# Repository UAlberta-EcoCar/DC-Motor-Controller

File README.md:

# DC-Motor-Controller
Our custom DC brushed motor controller

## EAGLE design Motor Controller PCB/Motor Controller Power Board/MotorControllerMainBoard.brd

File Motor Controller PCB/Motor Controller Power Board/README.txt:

If we deside to use an external mountable PCB for the voltage regulators,
it'll go here.

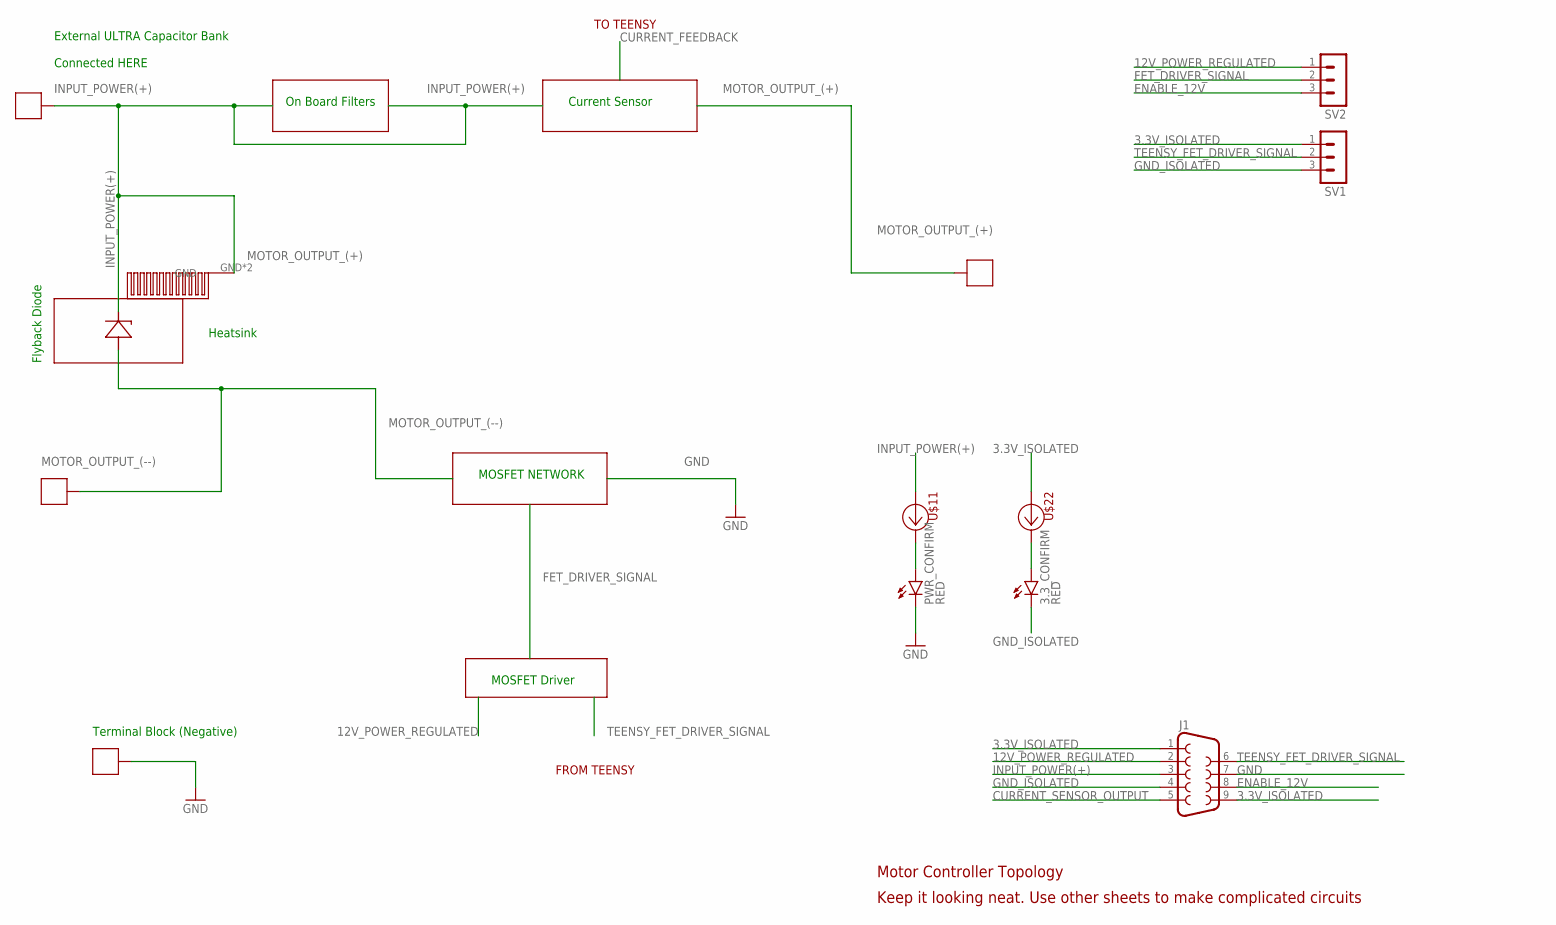
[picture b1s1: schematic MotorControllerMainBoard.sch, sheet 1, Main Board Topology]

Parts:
3.3_CONFIRM: RED; LED-1206
J1: DB9FEMALE; DB9
PWR_CONFIRM: RED; LED-1206
SV1, SV2: MA03-1
U$5: FLYBACK; TO
U$11, U$22: AL5809-20S1-7; SOD-123
U$12, U$14, U$15, U$16: 74650073R
U$23: DA-T263-101E

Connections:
3.3V_ISOLATED: J1.1, J1.9, SV1.1, U$22.A; also elsewhere on the board
12V_POWER_REGULATED: J1.2, SV2.1; also elsewhere on the board
CURRENT_SENSOR_OUTPUT: J1.5; also elsewhere on the board
ENABLE_12V: J1.8, SV2.3; also elsewhere on the board
FET_DRIVER_SIGNAL: SV2.2; also elsewhere on the board
GND: J1.7, PWR_CONFIRM.C, U$15.P$1, U$15.P$2, U$15.P$3, U$15.P$4; also elsewhere on the board
GND_ISOLATED: 3.3_CONFIRM.C, J1.4, SV1.3; also elsewhere on the board
INPUT_POWER(+): J1.3, U$5.CATHODE, U$11.A, U$14.P$1, U$14.P$2, U$14.P$3, U$14.P$4, U$23.GND, U$23.GND2\; also elsewhere on the board
MOTOR_OUTPUT_(+): U$16.P$1, U$16.P$2, U$16.P$3, U$16.P$4; also elsewhere on the board
MOTOR_OUTPUT_(--): U$5.ANODE, U$12.P$1, U$12.P$2, U$12.P$3, U$12.P$4; also elsewhere on the board
unnamed: 3.3_CONFIRM.A, U$22.C
unnamed: PWR_CONFIRM.A, U$11.C
TEENSY_FET_DRIVER_SIGNAL: J1.6, SV1.2; also elsewhere on the board

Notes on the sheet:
Current Sensor
On Board Filters
Flyback Diode
MOSFET NETWORK
MOSFET Driver
TO TEENSY
FROM TEENSY
External ULTRA Capacitor Bank Connected HERE
Motor Controller Topology
Keep it looking neat. Use other sheets to make complicated circuits
Terminal Block (Negative)
Heatsink

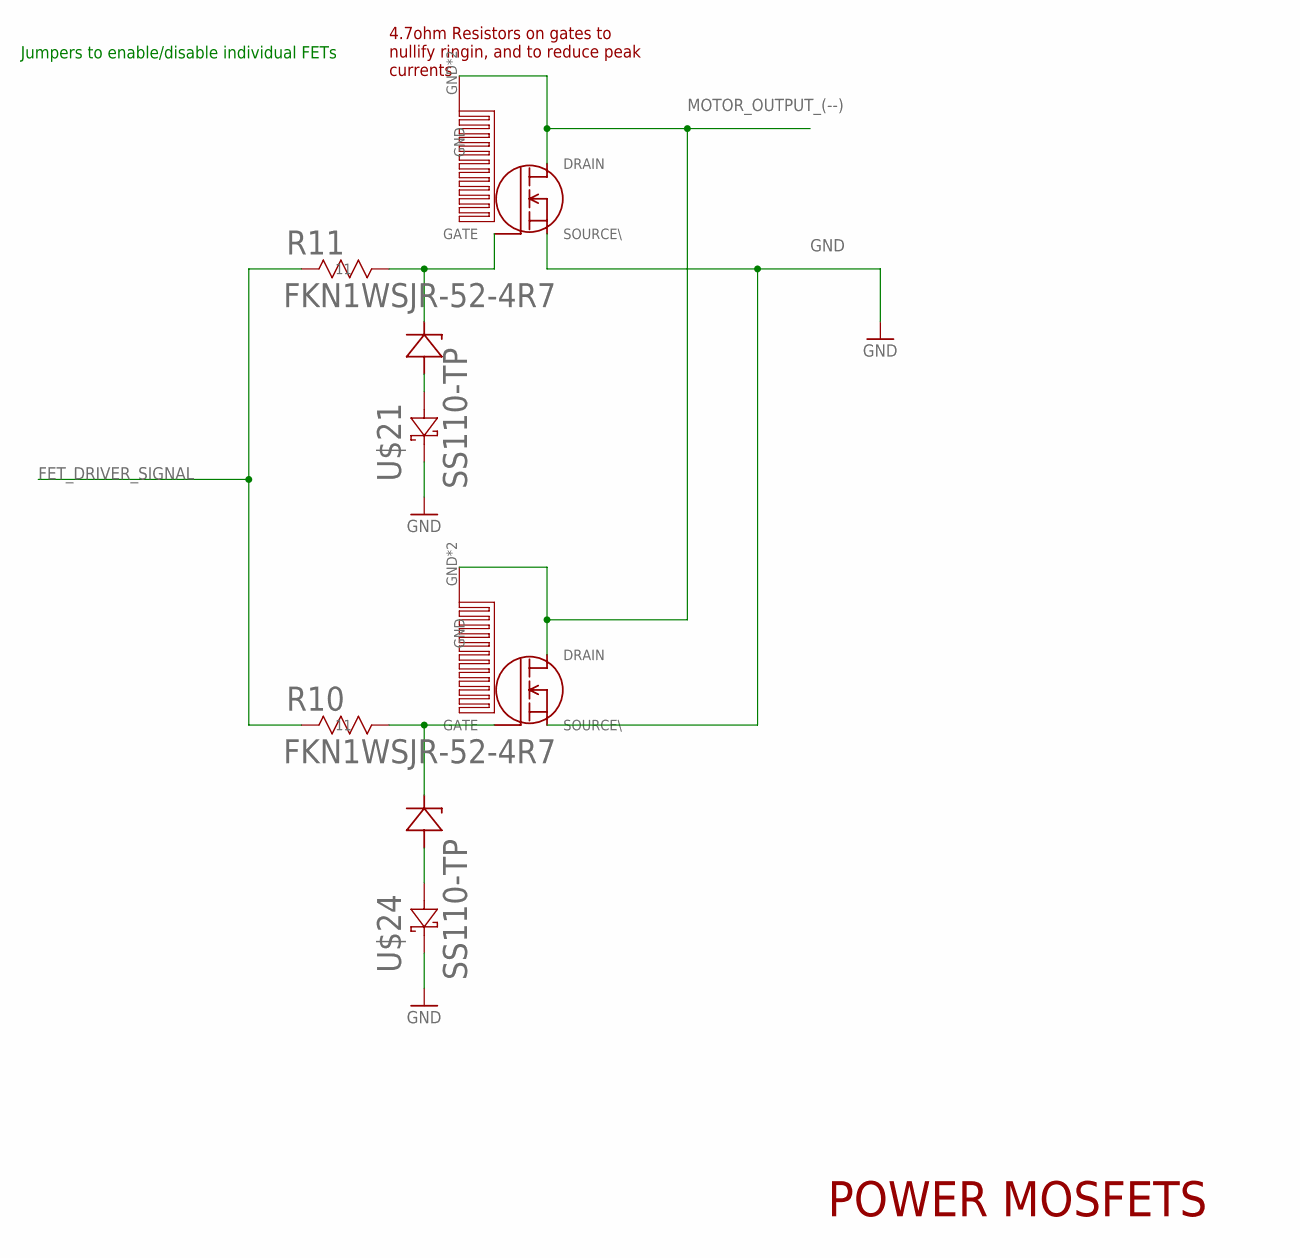
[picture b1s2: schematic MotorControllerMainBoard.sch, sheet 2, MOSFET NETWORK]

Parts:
R10, R11: FKN1WSJR-52-4R7; YAG_FKN50
U$1, U$2: IPB015N08N5ATMA1
U$3, U$4: DA-T263-101E
U$7, U$20: SMBJ15CD; SMB-DIODE
U$21, U$24: SS110-TP; SMA-DIODE

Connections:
FET_DRIVER_SIGNAL: R10.1 (11), R11.1 (11); also elsewhere on the board
GND: U$1.SOURCE (SOURCE\), U$2.SOURCE (SOURCE\), U$21.C (CATHODE), U$24.C (CATHODE); also elsewhere on the board
MOTOR_OUTPUT_(--): U$1.DRAIN, U$2.DRAIN, U$3.GND, U$3.GND2\, U$4.GND, U$4.GND2\; also elsewhere on the board
unnamed: U$7.A (ANODE), U$24.A (ANODE)
unnamed: R10.2 (22), U$2.GATE, U$7.C (CATHODE)
unnamed: U$20.A (ANODE), U$21.A (ANODE)
unnamed: R11.2 (22), U$1.GATE, U$20.C (CATHODE)

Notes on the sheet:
POWER MOSFETS
Jumpers to enable/disable individual FETs
4.7ohm Resistors on gates to nullify ringin, and to reduce peak currents

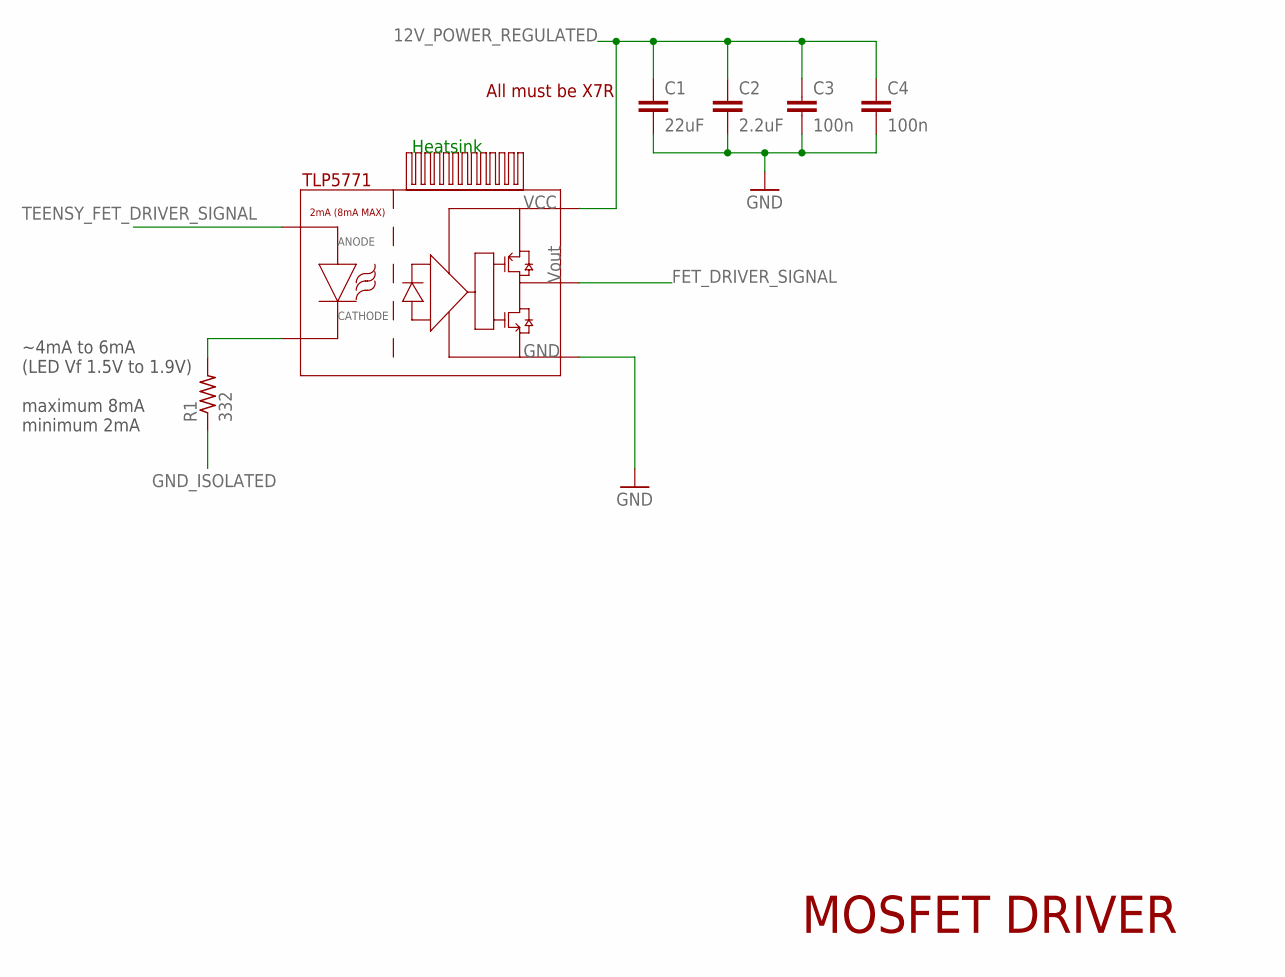
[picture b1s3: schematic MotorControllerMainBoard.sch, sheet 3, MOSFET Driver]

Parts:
C1: 22uF; C1210
C2: 2.2uF; C0805
C3, C4: 100n; C0603
R1: 332; R0805
U$17: TLP5771; SOIC-6(TLP5771)
U$25: LTN20069

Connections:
12V_POWER_REGULATED: C1.1, C2.1, C3.1, C4.1, U$17.6.VCC; also elsewhere on the board
FET_DRIVER_SIGNAL: U$17.5.VOUT; also elsewhere on the board
GND: C1.2, C2.2, C3.2, C4.2, U$17.4.GND; also elsewhere on the board
GND_ISOLATED: R1.1; also elsewhere on the board
unnamed: R1.2, U$17.2.NC (3.CATHODE), U$17.3:CATHODE (3.CATHODE)
TEENSY_FET_DRIVER_SIGNAL: U$17.1.ANODE; also elsewhere on the board

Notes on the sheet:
MOSFET DRIVER
All must be X7R
~4mA to 6mA (LED Vf 1.5V to 1.9V) maximum 8mA minimum 2mA
Heatsink

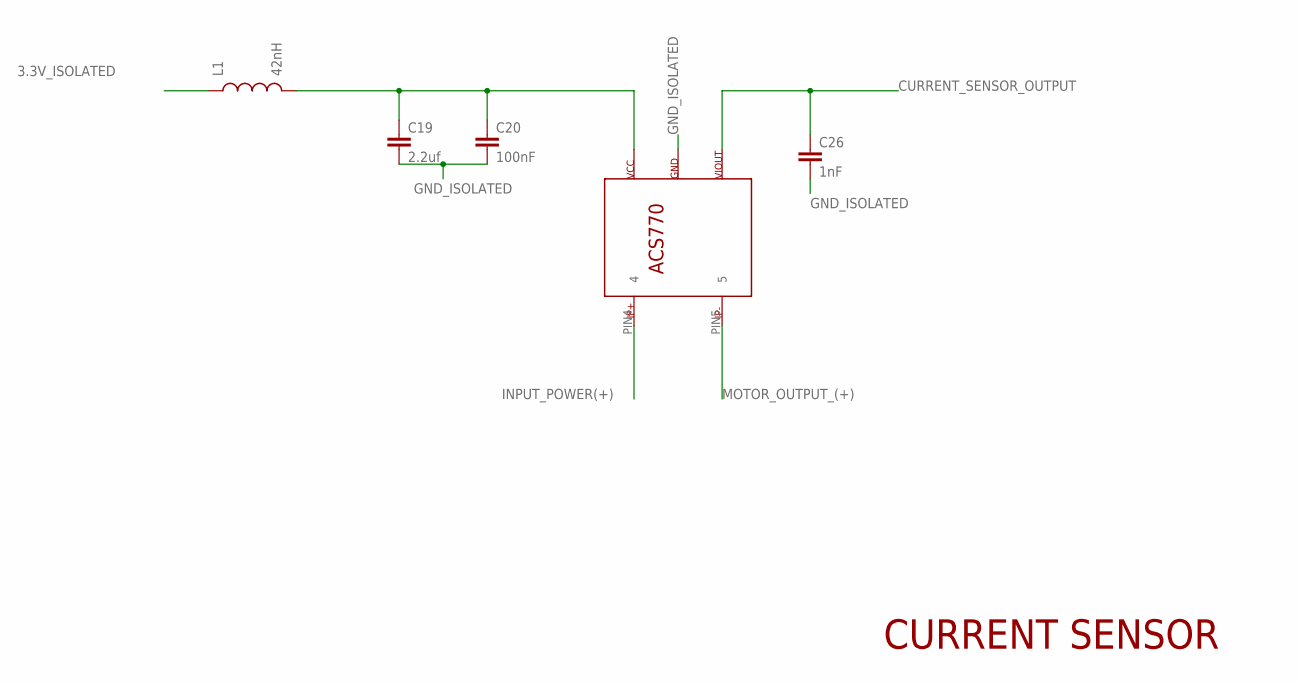
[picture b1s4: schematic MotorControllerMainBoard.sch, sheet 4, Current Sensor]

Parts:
C19: 2.2uf; C0805
C20: 100nF; C0805
C26: 1nF; C0805
L1: 42nH; 0805
U$9: ACS770LCB_CURRENTSENSOR

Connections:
3.3V_ISOLATED: L1.1; also elsewhere on the board
CURRENT_SENSOR_OUTPUT: C26.1, U$9.PIN3 (3); also elsewhere on the board
GND_ISOLATED: C19.2, C20.2, C26.2, U$9.PIN2 (2); also elsewhere on the board
INPUT_POWER(+): U$9.PIN4 (4); also elsewhere on the board
MOTOR_OUTPUT_(+): U$9.PIN5 (5); also elsewhere on the board
unnamed: C19.1, C20.1, L1.2, U$9.PIN1 (1)

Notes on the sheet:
CURRENT SENSOR

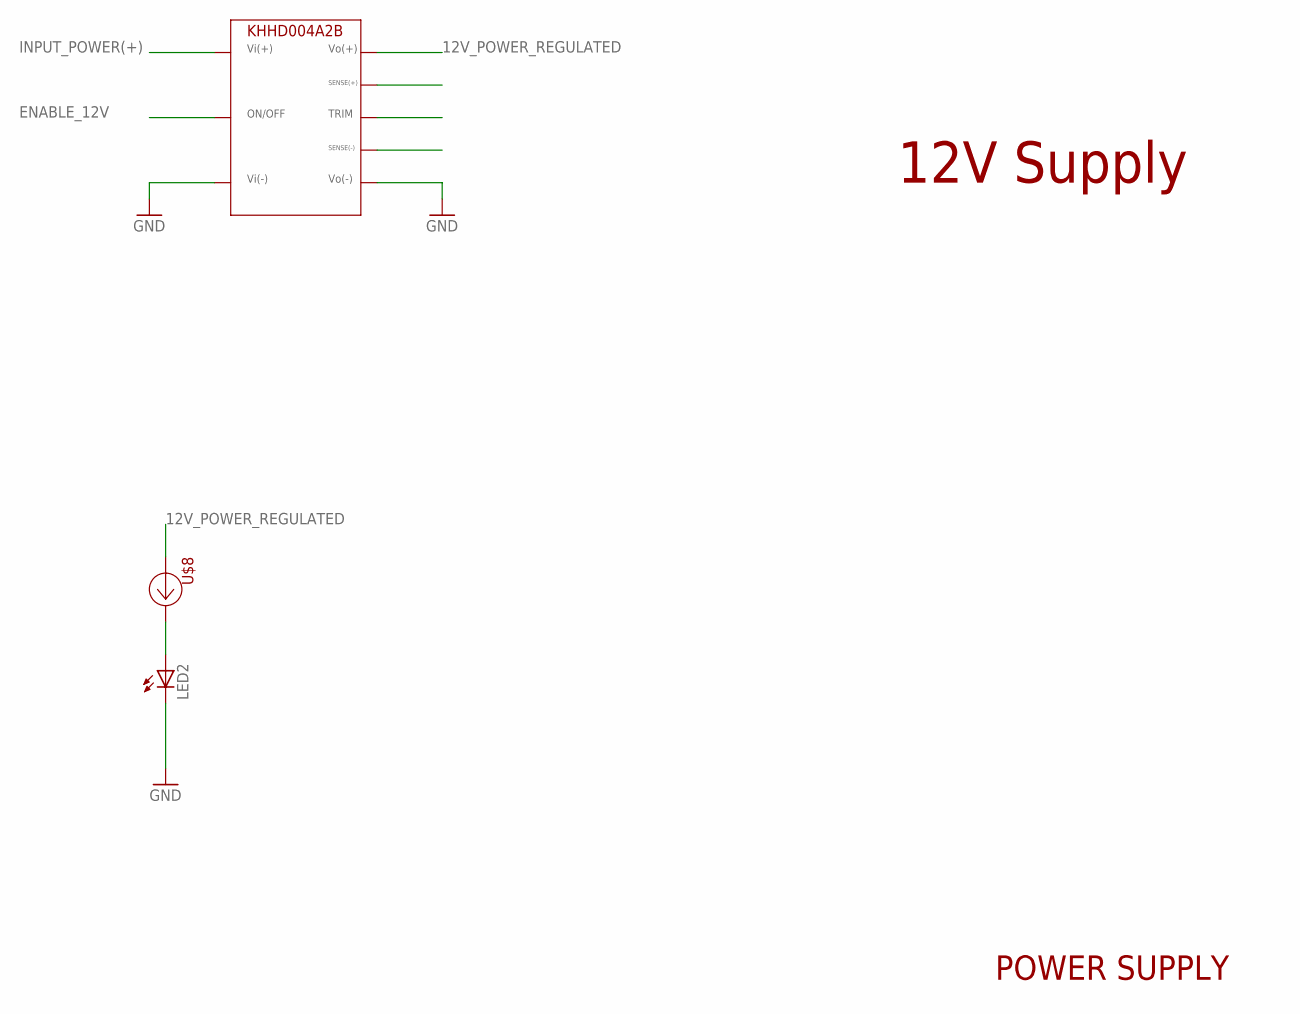
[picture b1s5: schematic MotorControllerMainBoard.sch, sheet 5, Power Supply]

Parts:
LED2: LED1206; LED-1206
U$6: KHHD004A2B
U$8: AL5809-20S1-7; SOD-123

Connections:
12V_POWER_REGULATED: U$6.VO+ (VO(+)), U$8.A; also elsewhere on the board
ENABLE_12V: U$6.ON/OFF; also elsewhere on the board
GND: LED2.C, U$6.VI- (VI(-)), U$6.VO- (VO(-)); also elsewhere on the board
INPUT_POWER(+): U$6.VI+ (VI(+)); also elsewhere on the board
unnamed: LED2.A, U$8.C

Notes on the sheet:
POWER SUPPLY
12V Supply

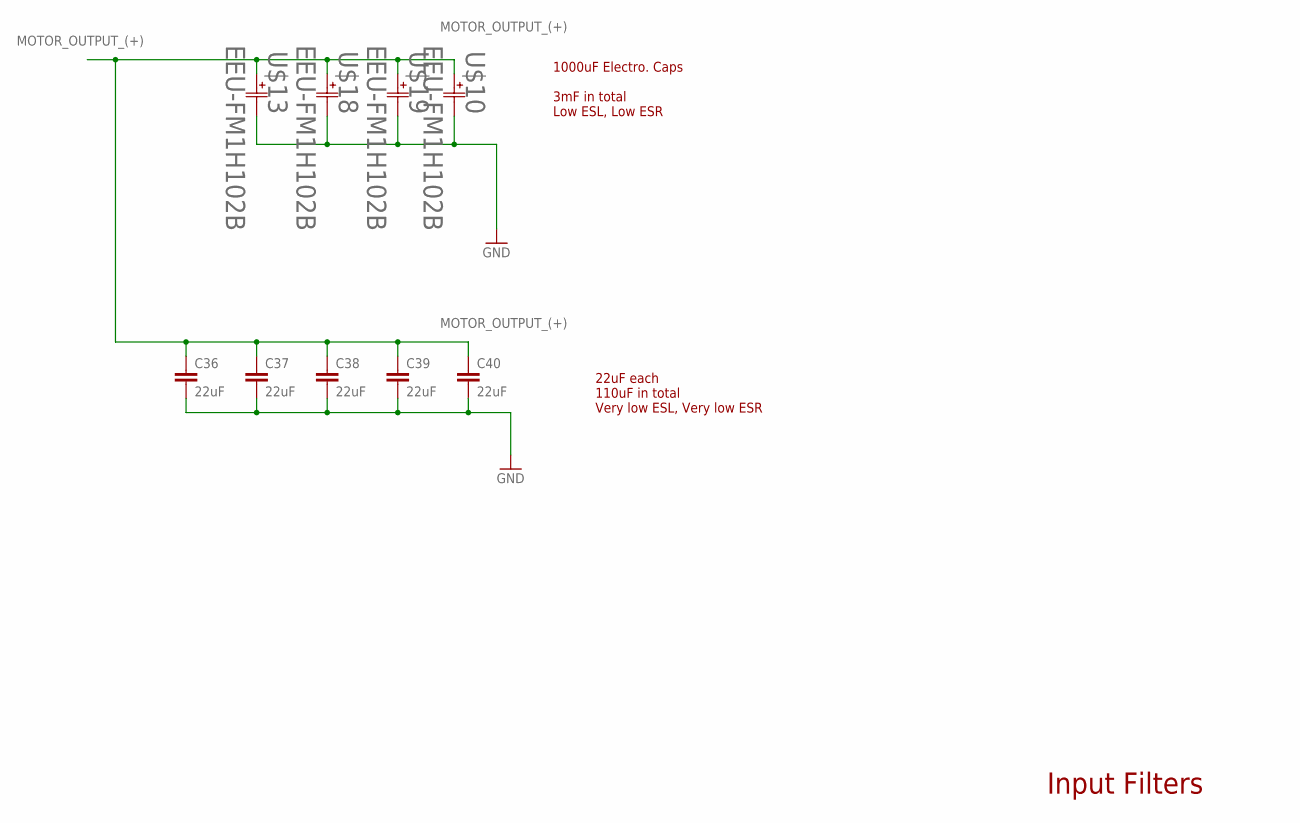
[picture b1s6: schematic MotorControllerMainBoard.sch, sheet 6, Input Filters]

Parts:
C36, C37, C38, C39, C40: 22uF; C1210
U$10, U$13, U$18, U$19: EEU-FM1H102B

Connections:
GND: C36.2, C37.2, C38.2, C39.2, C40.2, U$10.NEGATIVE, U$13.NEGATIVE, U$18.NEGATIVE, U$19.NEGATIVE; also elsewhere on the board
MOTOR_OUTPUT_(+): C36.1, C37.1, C38.1, C39.1, C40.1, U$10.POSITIVE, U$13.POSITIVE, U$18.POSITIVE, U$19.POSITIVE; also elsewhere on the board

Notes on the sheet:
Input Filters
22uF each 110uF in total Very low ESL, Very low ESR
1000uF Electro. Caps 3mF in total Low ESL, Low ESR

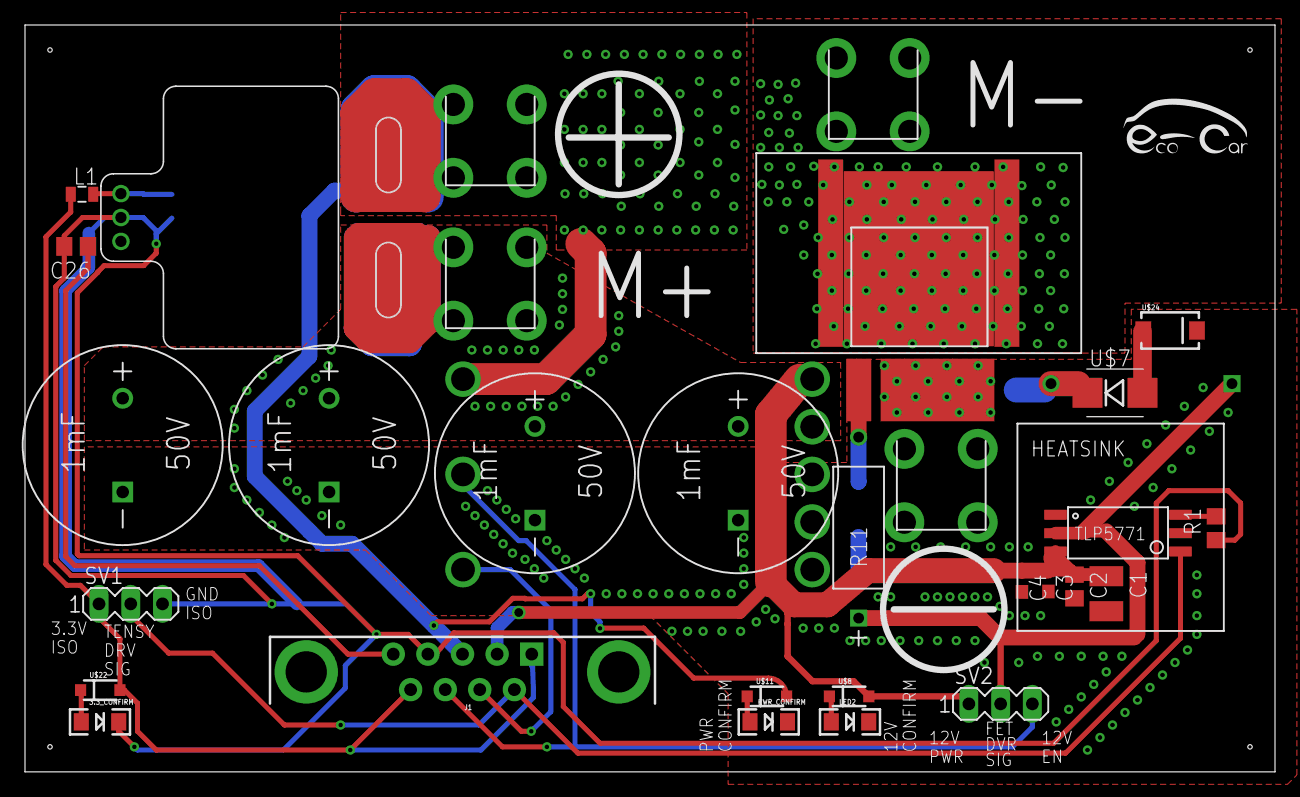
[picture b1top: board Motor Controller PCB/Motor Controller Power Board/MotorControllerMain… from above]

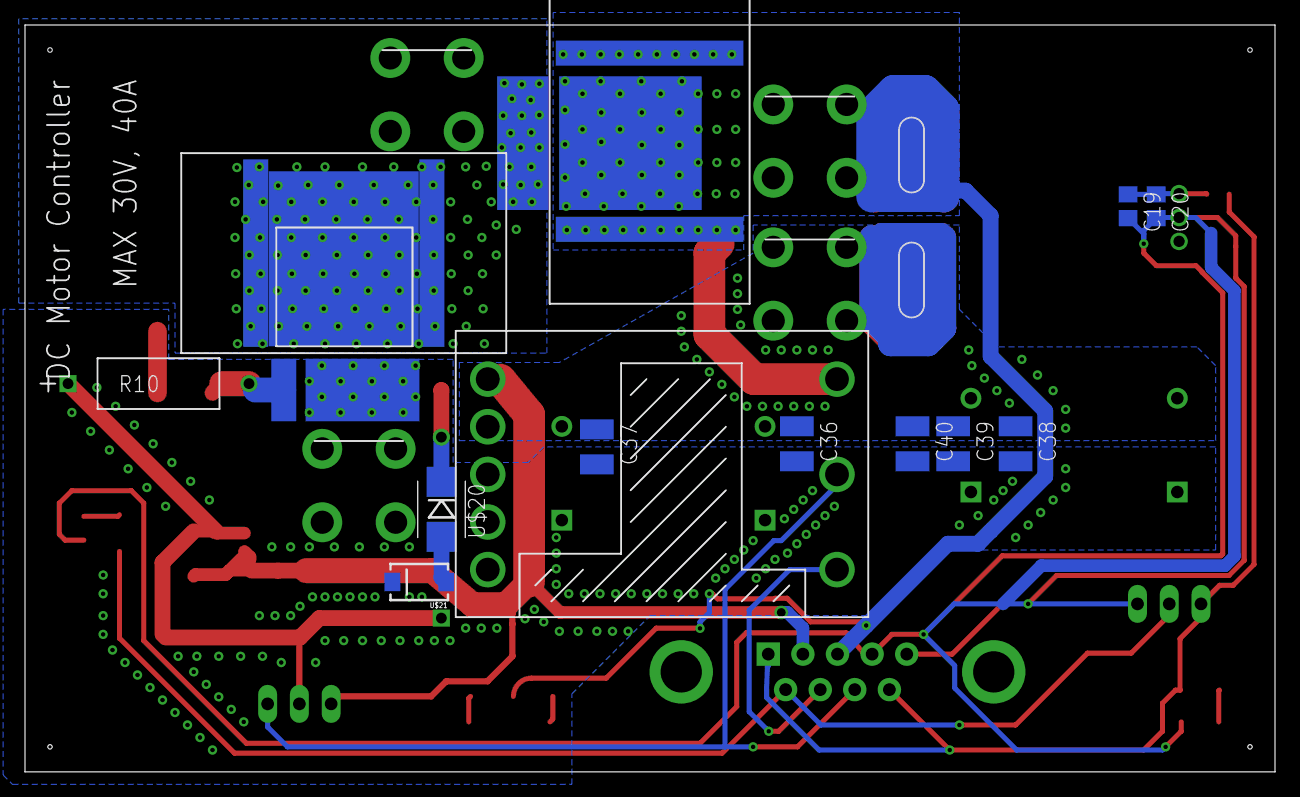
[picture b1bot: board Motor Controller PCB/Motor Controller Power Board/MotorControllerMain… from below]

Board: 2 copper layers, 99.9 x 59.6 mm, 48 parts (15 on the bottom side), 20 nets.

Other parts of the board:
U$26: LOGO

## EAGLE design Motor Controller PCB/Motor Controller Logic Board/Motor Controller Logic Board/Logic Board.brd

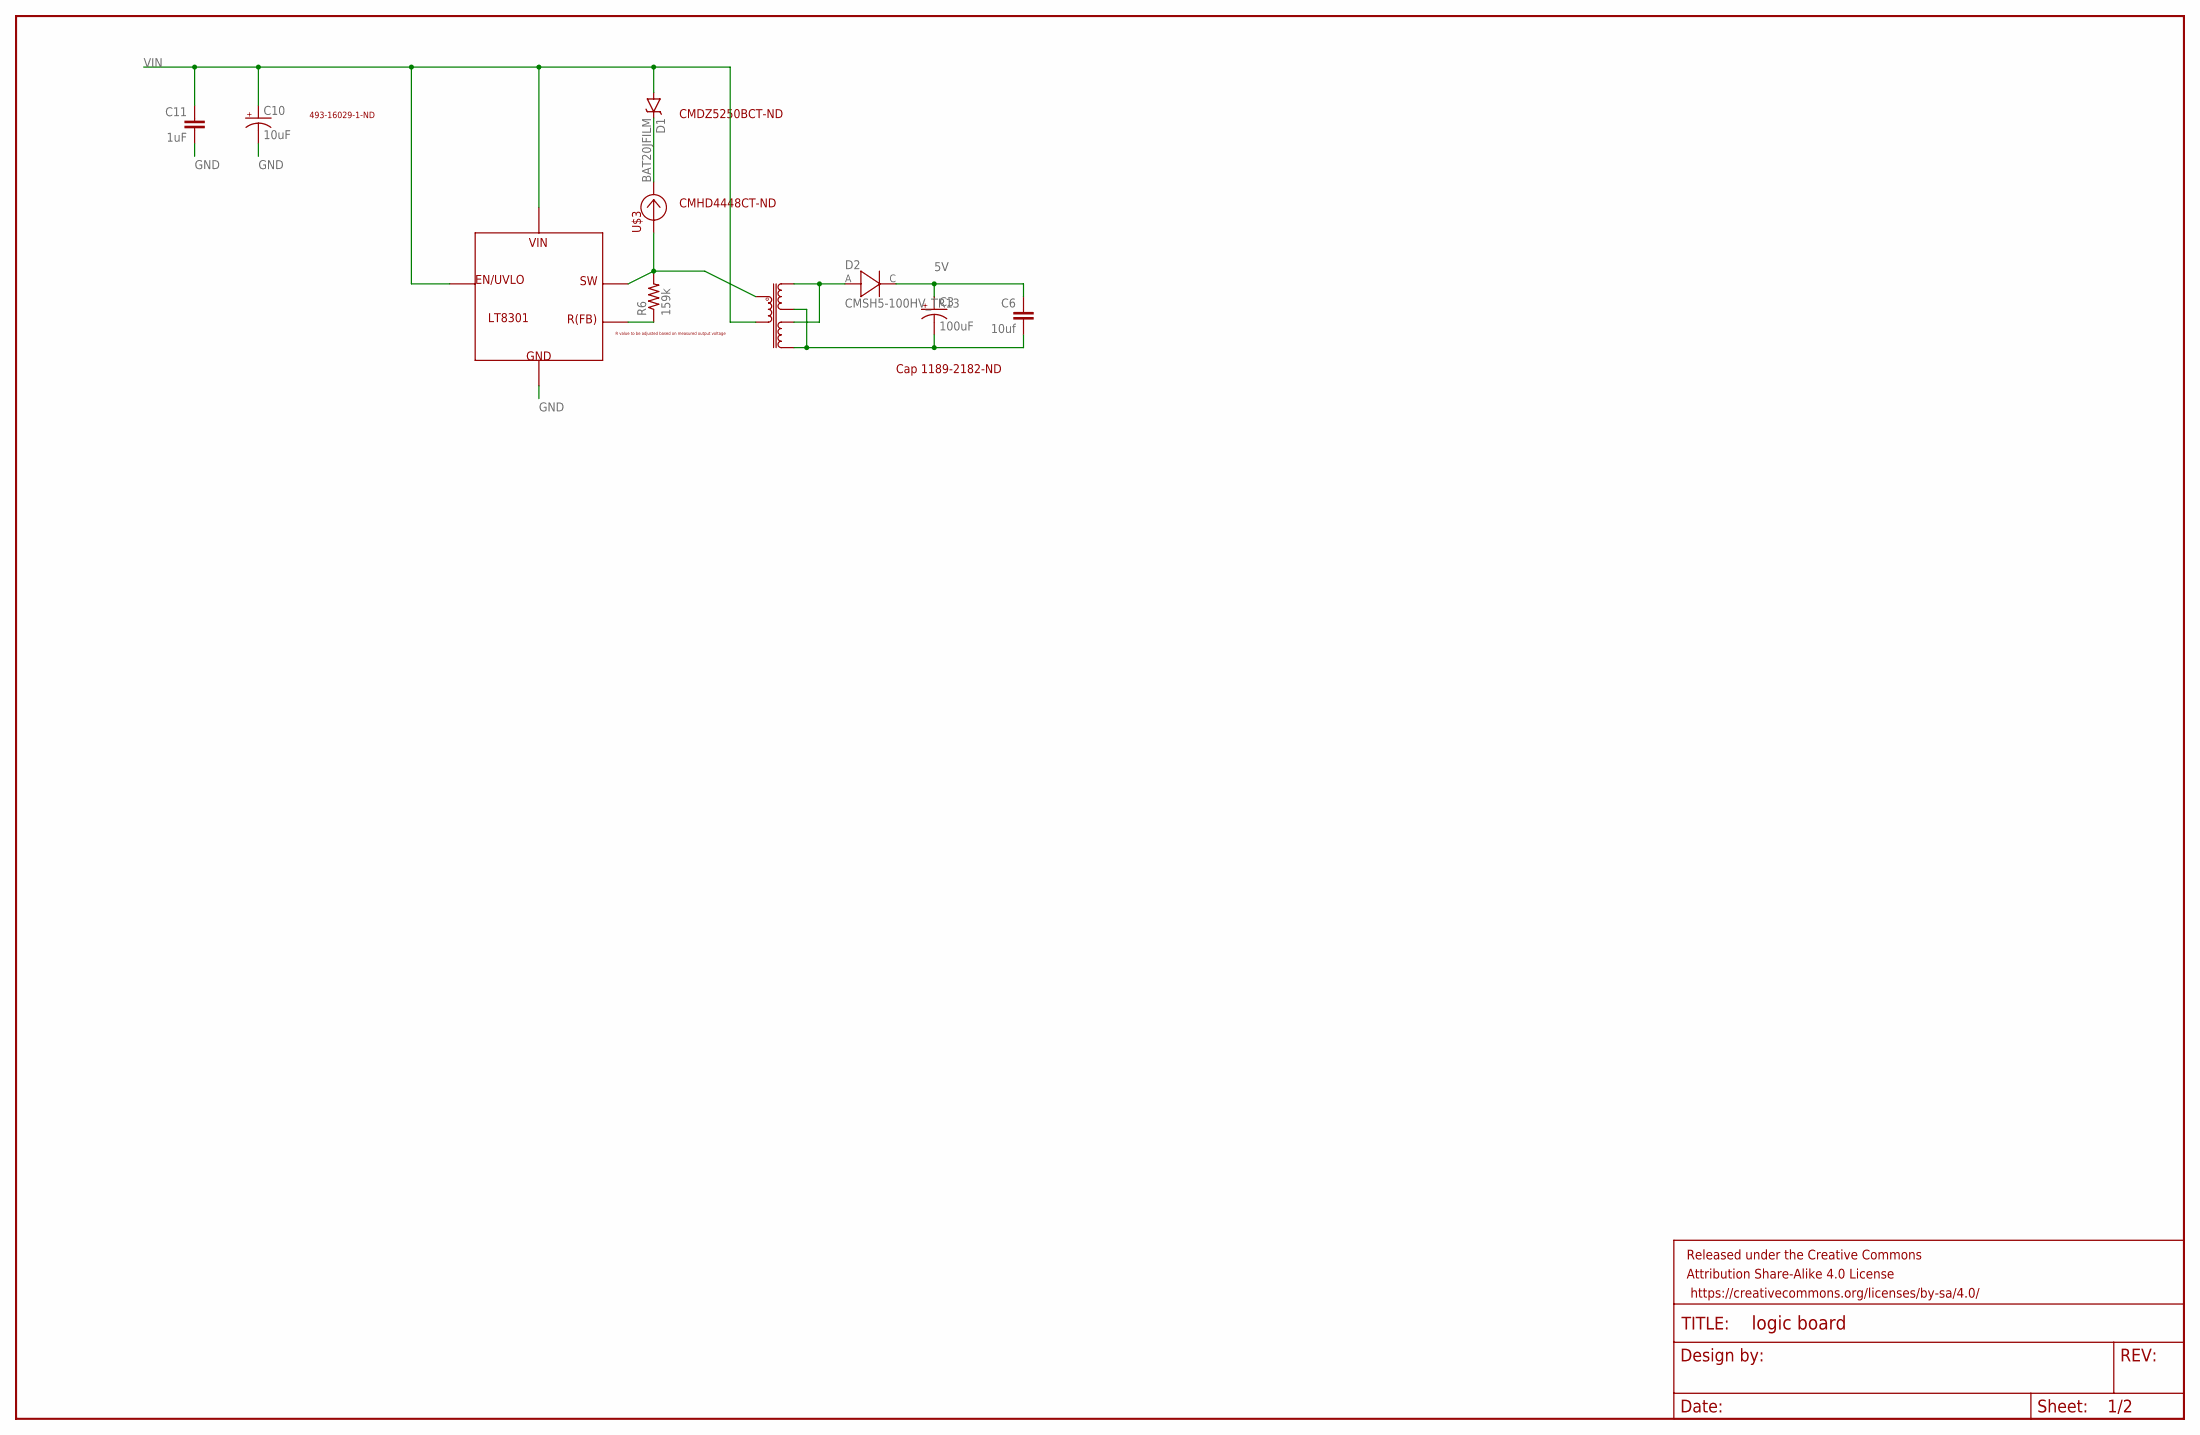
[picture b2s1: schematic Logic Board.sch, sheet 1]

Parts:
C3: 100uF; CPOL-RADIAL-2.5MM-6.5MM
C6: 10uf; C0805
C10: 10uF; CPOL-RADIAL-100UF-25V
C11: 1uF; C0805
D1: BAT20JFILM; SOD-323
D2: CMSH5-100HV_TR13; DIOM794X590X262L114X300N
FRAME1: FRAME-LEDGER; CREATIVE_COMMONS
R6: 159k; R0805
U$1: LT8301; TSOT-23-5
U$2: 750313974; 750313974_TRANSFORMER
U$3: AL5809-20S1-7; SOD-123

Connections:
5V: C3.1 (+), C6.1, D2.C; also elsewhere on the board
GND: C10.2 (-), C11.2, U$1.2.GND (GND); also elsewhere on the board
unnamed: R6.2, U$1.4.SW (SW), U$2.1, U$3.A
unnamed: D2.A, U$2.5, U$2.6
unnamed: C3.2 (-), C6.2, U$2.7, U$2.8
unnamed: R6.1, U$1.3.RFB (RFB)
unnamed: D1.C, U$3.C
VIN: C10.1 (+), C11.1, D1.A, U$1.1.EN/UVLO (EN/UVLO), U$1.5.VIN (VIN), U$2.4

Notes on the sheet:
Cap 1189-2182-ND
CMDZ5250BCT-ND
CMHD4448CT-ND
R value to be adjusted based on measured output voltage
493-16029-1-ND

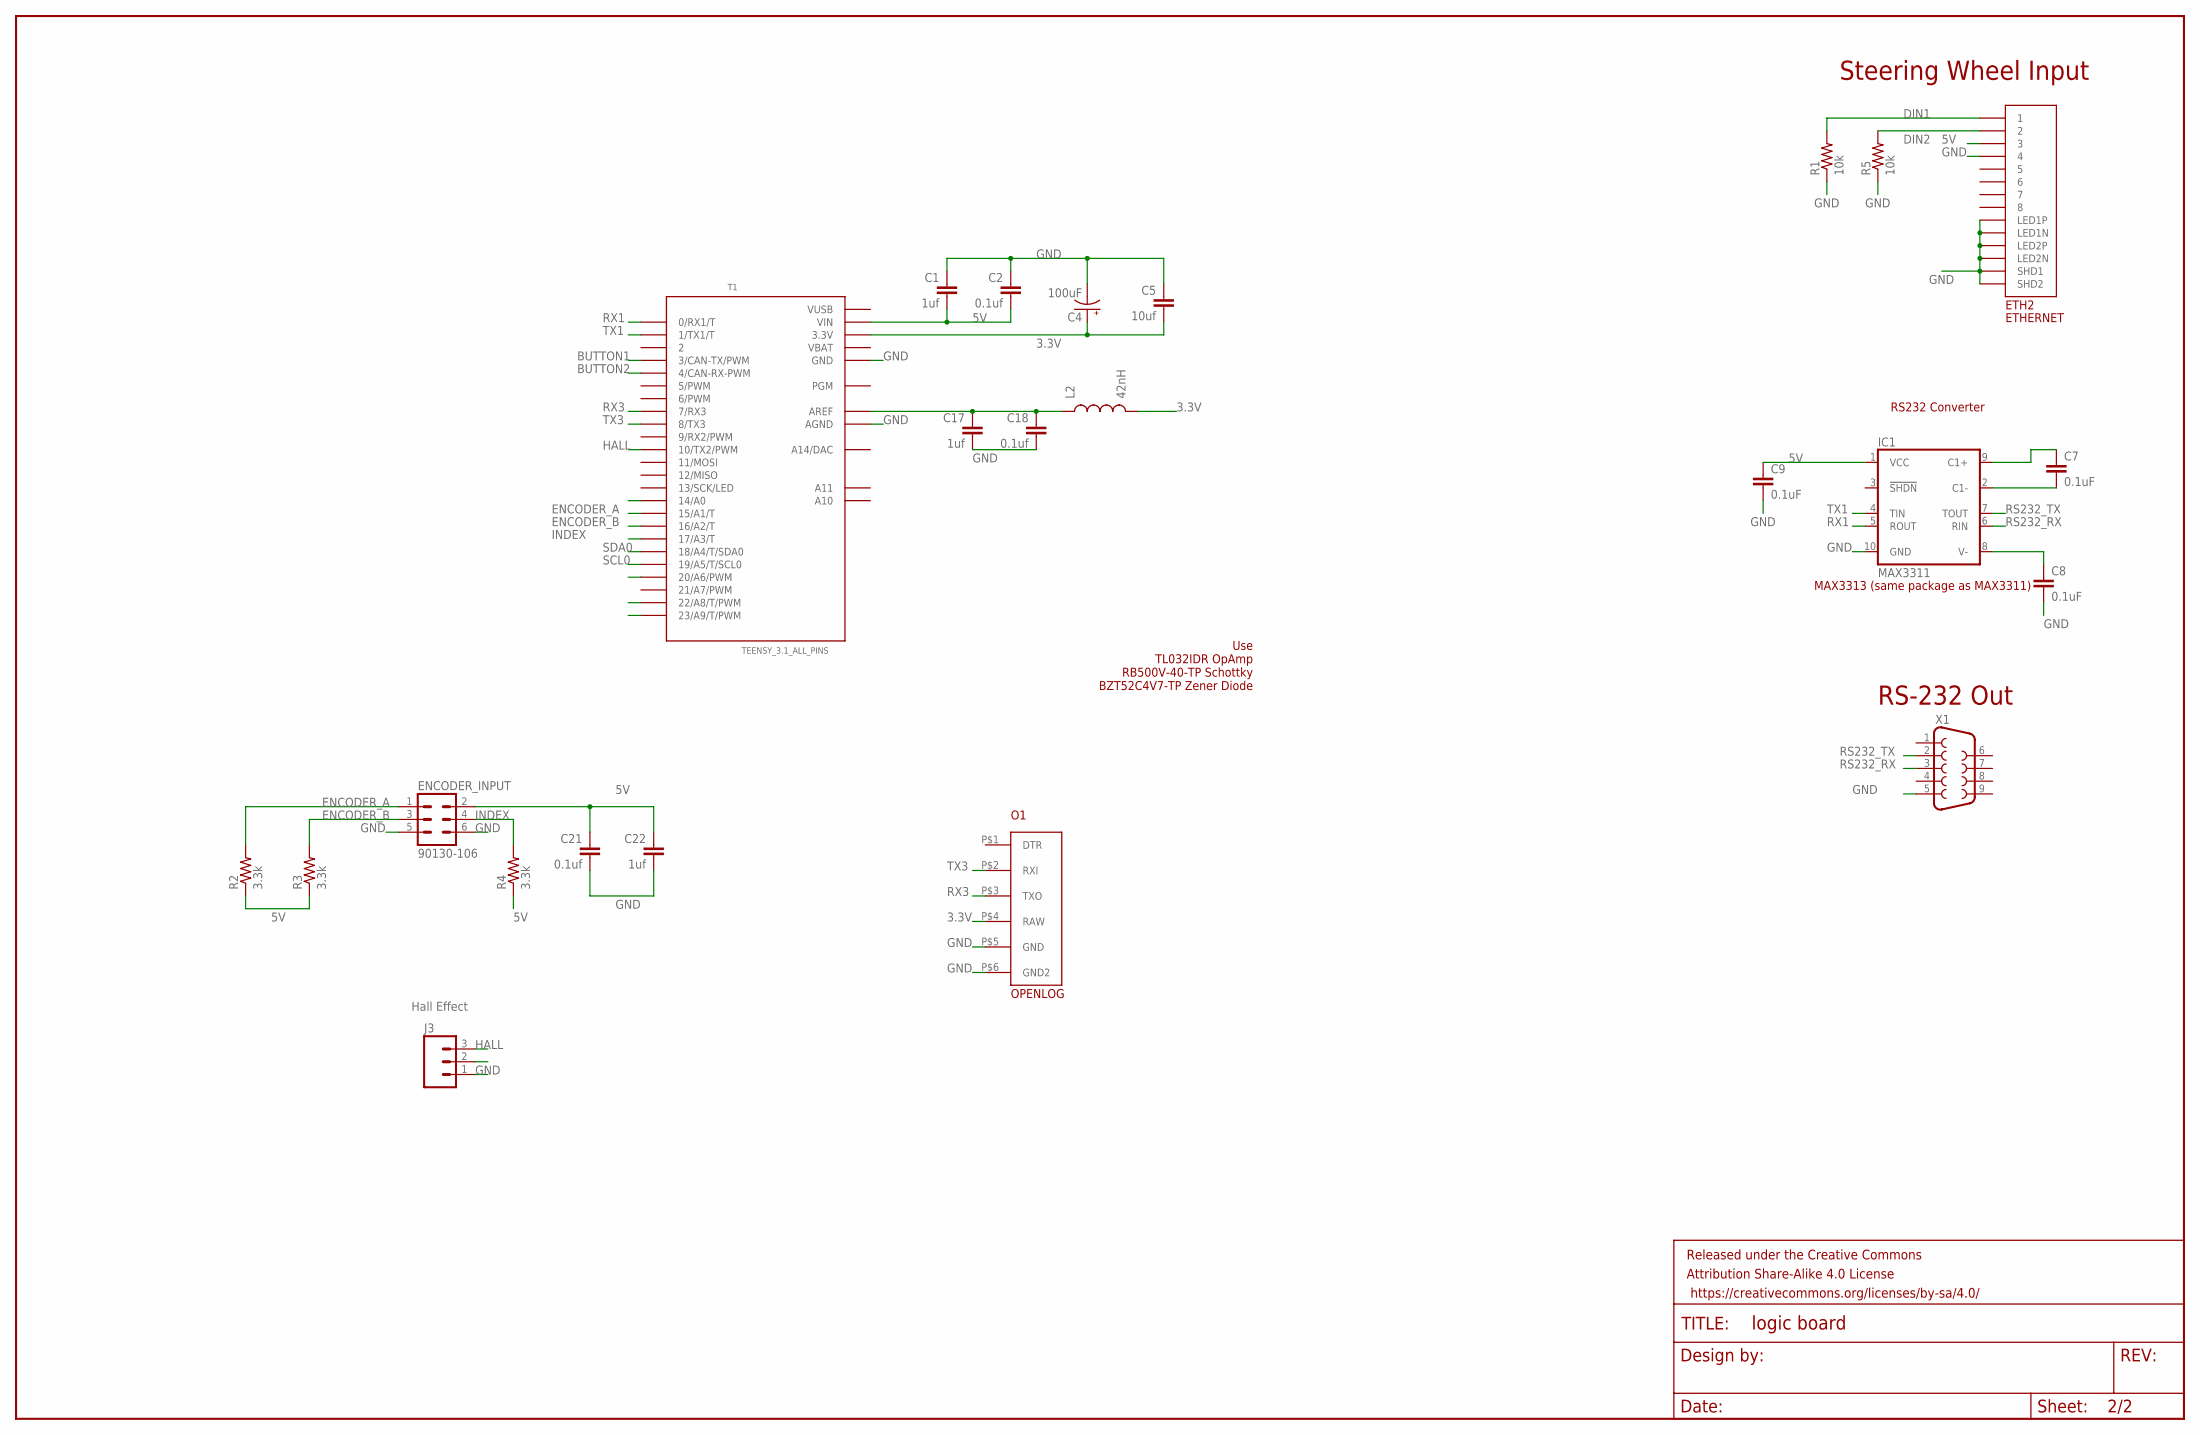
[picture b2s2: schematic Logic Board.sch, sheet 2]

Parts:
C1, C17, C22: 1uf; C0805
C2, C18, C21: 0.1uf; C0805
C4: 100uF; CPOL-RADIAL-2.5MM-6.5MM
C5: 10uf; C0805
C7, C8, C9: 0.1uF; 0805
ENCODER_INPUT: 90130-106; 90130-1?06
ETH2: ETHERNET; A122645-ND
FRAME2: FRAME-LEDGER; CREATIVE_COMMONS
IC1: MAX3311; UMAX10
J3: M03PTH; 1X03
L2: 42nH; 0805
O1: OPENLOG
R1, R5: 10k; 0805
R2, R3, R4: 3.3k; R0805
T1: TEENSY_3.1_ALL_PINS; TEENSY3-ALL_PINS
X1: F09HP

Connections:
3.3V: C4.1 (+), C5.2, L2.2, O1.P$4 (RAW), T1.3.3V, T1.3.3V1 (3.3V)
5V: C1.2, C2.2, C9.1, C21.1, C22.1, ENCODER_INPUT.2, ETH2.P$3 (3), IC1.1 (VCC), J3.2, R2.1, R3.1, R4.1, T1.VIN; also elsewhere on the board
BUTTON1: T1.3 (3/CAN-TX/PWM)
BUTTON2: T1.4 (4/CAN-RX-PWM)
COAST_ENABLE: T1.20/A6 (20/A6/PWM)
CURRENT_FEEDBACK: T1.14/A0
DIN1: ETH2.P$1 (1), R1.2
DIN2: ETH2.P$2 (2), R5.2
ENCODER_A: ENCODER_INPUT.1, R2.2, T1.15/A1 (15/A1/T)
ENCODER_B: ENCODER_INPUT.3, R3.2, T1.16/A2 (16/A2/T)
GND: C1.1, C2.1, C4.2 (-), C5.1, C8.2, C9.2, C17.2, C18.2, C21.2, C22.2, ENCODER_INPUT.5, ENCODER_INPUT.6, ETH2.P$4 (4), ETH2.P$9 (LED1N), ETH2.P$10 (LED1P), ETH2.P$11 (LED2N), ETH2.P$12 (LED2P), ETH2.P$13 (SHD1), ETH2.P$14 (SHD2), IC1.10 (GND), J3.1, O1.P$5 (GND), O1.P$6 (GND2), R1.1, R5.1, T1.AGND, T1.GND, T1.GND1 (GND), X1.5; also elsewhere on the board
HALL: J3.3, T1.10 (10/TX2/PWM)
INDEX: ENCODER_INPUT.4, R4.2, T1.17/A3 (17/A3/T)
unnamed: C7.1, IC1.9 (C1+)
unnamed: C7.2, IC1.2 (C1-)
unnamed: C8.1, IC1.8 (V-)
unnamed: C17.1, C18.1, L2.1, T1.AREF
RS232_RX: IC1.6 (RIN), X1.3
RS232_TX: IC1.7 (TOUT), X1.2
RX1: IC1.5 (ROUT), T1.0 (0/RX1/T)
RX3: O1.P$3 (TXO), T1.7 (7/RX3)
SCL0: T1.19/A5 (19/A5/T/SCL0)
SDA0: T1.18/A4 (18/A4/T/SDA0)
SUPPLY_VOLTAGE: T1.22/A8 (22/A8/T/PWM)
TEENSY_FET_DRIVER_SIGNAL: T1.23/A9 (23/A9/T/PWM)
TX1: IC1.4 (TIN), T1.1 (1/TX1/T)
TX3: O1.P$2 (RXI), T1.8 (8/TX3)
VBAT: T1.VBAT
VUSB: T1.VUSB

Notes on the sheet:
Use TL032IDR OpAmp RB500V-40-TP Schottky BZT52C4V7-TP Zener Diode
Steering Wheel Input
RS232 Converter
MAX3313 (same package as MAX3311)
Hall Effect
RS-232 Out

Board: 2 copper layers, 36 parts (0 on the bottom side), 25 nets, no tracks yet.

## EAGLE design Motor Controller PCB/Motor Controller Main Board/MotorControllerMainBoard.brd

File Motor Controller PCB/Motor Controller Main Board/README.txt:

Schematic and Board files for the the motor controller here

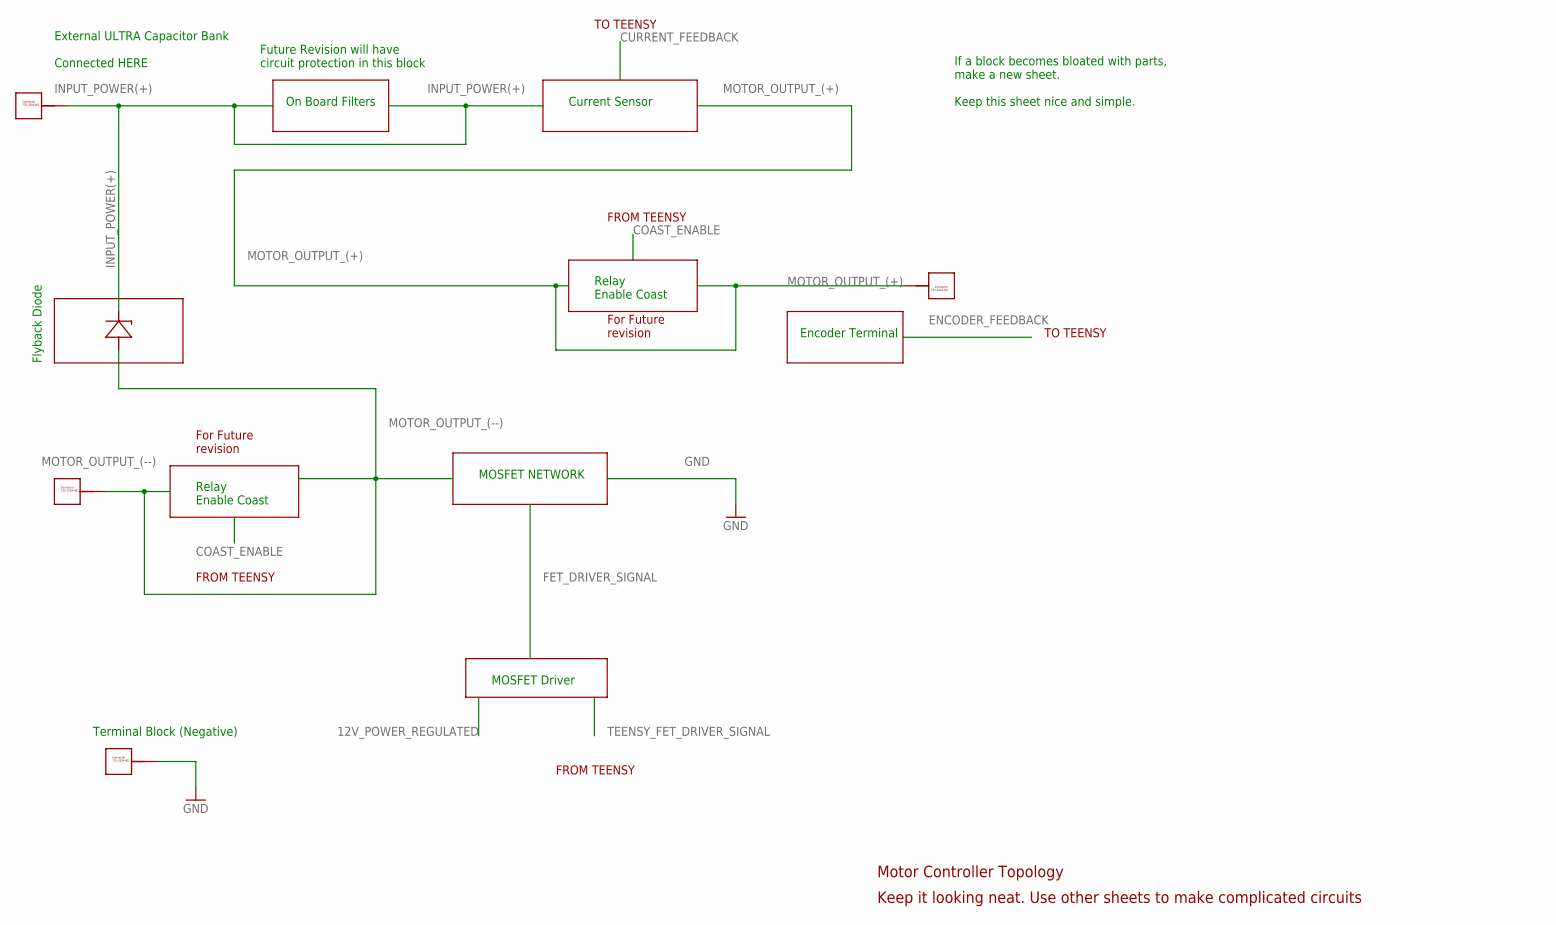
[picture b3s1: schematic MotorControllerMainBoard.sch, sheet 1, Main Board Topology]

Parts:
U$5: FLYBACK; TO
U$12, U$14, U$15, U$16: 732-3204-ND_CONNECTOR; 732-3204-ND

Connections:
GND: U$14.P$1, U$14.P$2, U$14.P$3, U$14.P$4, U$14.P$5, U$14.P$6, U$14.P$7, U$14.P$8, U$14.P$9, U$14.P$10; also elsewhere on the board
INPUT_POWER(+): U$5.CATHODE, U$12.P$1, U$12.P$2, U$12.P$3, U$12.P$4, U$12.P$5, U$12.P$6, U$12.P$7, U$12.P$8, U$12.P$9, U$12.P$10; also elsewhere on the board
MOTOR_OUTPUT_(+): U$15.P$1, U$15.P$2, U$15.P$3, U$15.P$4, U$15.P$5, U$15.P$6, U$15.P$7, U$15.P$8, U$15.P$9, U$15.P$10; also elsewhere on the board
MOTOR_OUTPUT_(--): U$5.ANODE, U$16.P$1, U$16.P$2, U$16.P$3, U$16.P$4, U$16.P$5, U$16.P$6, U$16.P$7, U$16.P$8, U$16.P$9, U$16.P$10; also elsewhere on the board

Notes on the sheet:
Current Sensor
On Board Filters
Flyback Diode
MOSFET NETWORK
If a block becomes bloated with parts, make a new sheet. Keep this sheet nice and simple.
MOSFET Driver
Encoder Terminal
TO TEENSY
FROM TEENSY
External ULTRA Capacitor Bank Connected HERE
Relay Enable Coast
Motor Controller Topology
Keep it looking neat. Use other sheets to make complicated circuits
For Future revision
Terminal Block (Negative)
Future Revision will have circuit protection in this block

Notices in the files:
parts and their libraries:
SparkFun-Capacitors: Licensing: Creative Commons ShareAlike 4.0 International - https://creativecommons.org/licenses/by-sa/4.0
SparkFun-Aesthetics: Released under the Creative Commons Attribution Share-Alike 4.0 License
SparkFun-Aesthetics: https://creativecommons.org/licenses/by-sa/4.0
